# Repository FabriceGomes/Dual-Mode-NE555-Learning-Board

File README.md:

# Dual-Mode-NE555-Learning-Board
A simple NE555 learning board with mono- and bistable modes, made for kids to solder, learn basics, and spark excitement for electronics.

This project presents a custom-designed printed circuit board built around two NE555 timer ICs, arranged to demonstrate two fundamental operating modes of the device. One NE555 is configured in monostable mode, while the second operates in bistable mode. Both circuits are designed to generate a visible one-second blink, making their behavior easy to observe and understand.

A deliberate design choice is the use of the J2 pin header as the trigger interface for the monostable NE555. Instead of implementing a mechanical switch, J2 allows the trigger to be activated using simple jumper caps. This keeps the board cost-effective, reduces mechanical wear, and makes assembly easier for beginners—while still letting participants experiment with trigger control.

The primary purpose of this PCB is educational. It was developed as a hands-on learning platform for children and teenagers, allowing them to solder the components themselves and explore basic electronics in a tangible, engaging way. By assembling the board, young participants learn about resistors, capacitors, integrated circuits, and how these elements interact to create timing functions. The contrasting modes of the two NE555s help illustrate how different circuit configurations lead to different behaviors, even when using the same building block.

Beyond its technical function, the project aims to spark curiosity and confidence in electronics through approachable, practical experience. The board’s layout is intentionally simple, robust, and visually structured to support beginners during assembly, troubleshooting, and experimentation. This combination of clear educational value, functional circuit design, and thoughtful cost-optimized features makes the PCB a versatile tool for workshops, maker events, and introductory electronics courses.

## License
This project is licensed under the MIT License – see the LICENSE file for details.

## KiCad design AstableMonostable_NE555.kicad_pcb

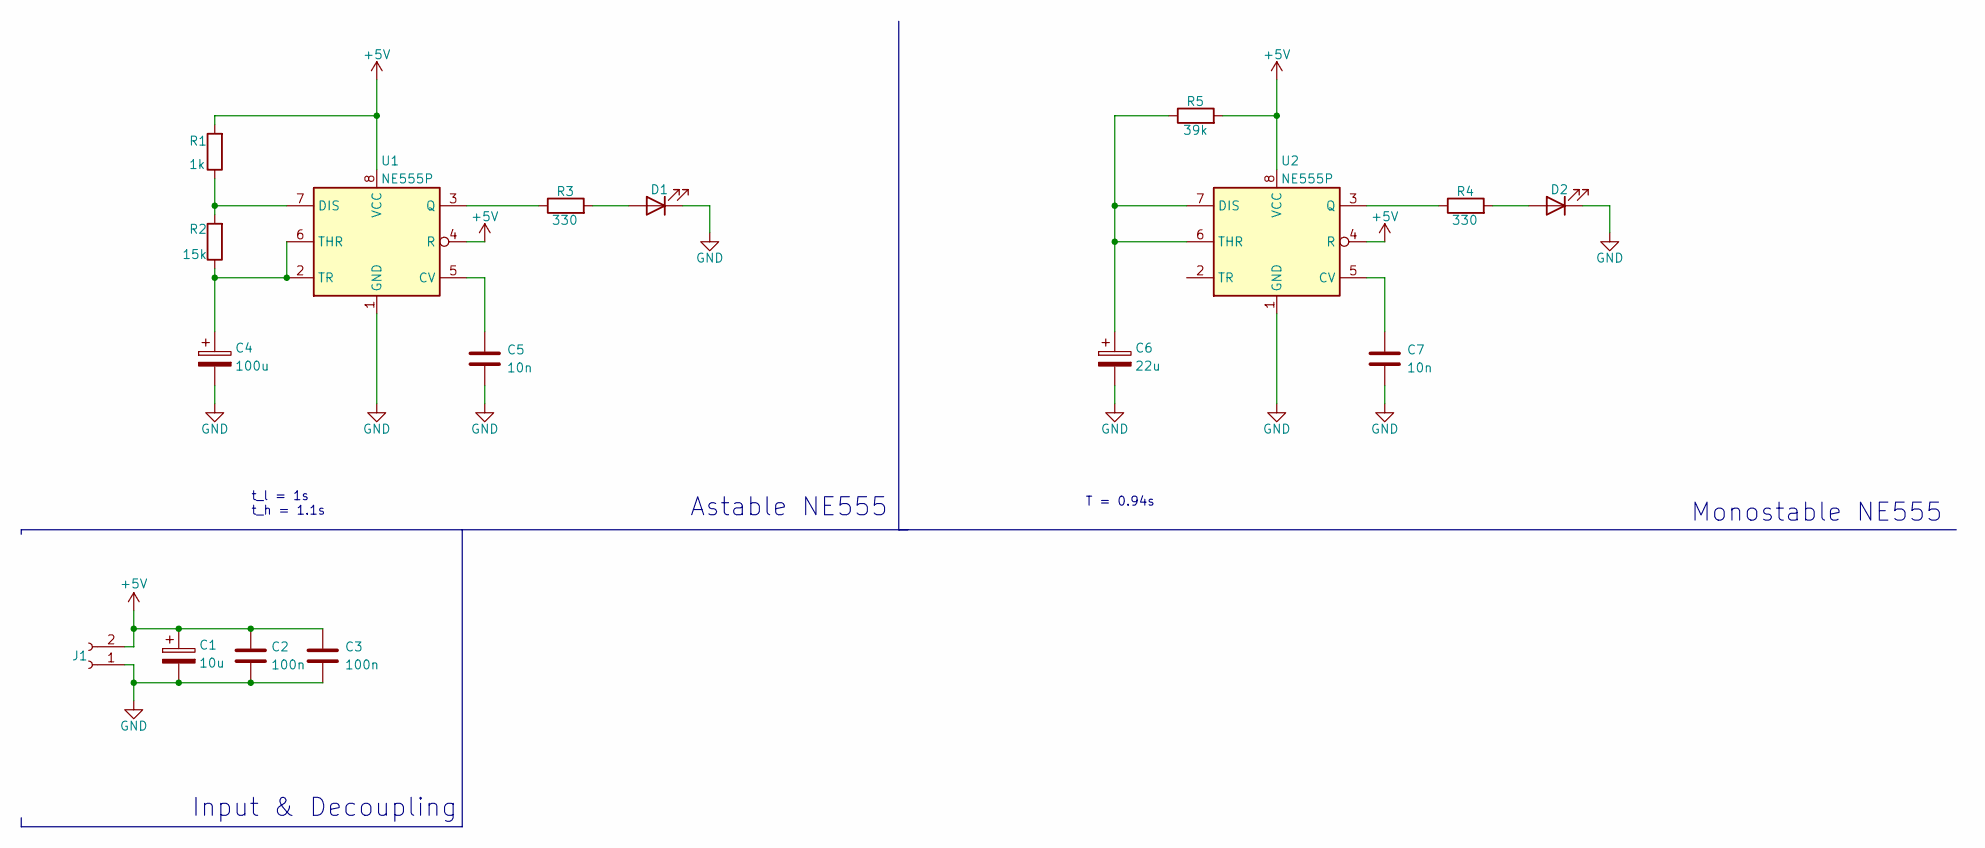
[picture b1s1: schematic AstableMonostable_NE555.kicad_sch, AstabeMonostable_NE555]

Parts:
C1: 10u; CP_Elec_5x5.4
C2, C3: 100n; C_1206_3216Metric_Pad1.33x1.80mm_HandSolder
C4: 100u; CP_Elec_6.3x7.7
C5, C7: 10n; C_1206_3216Metric_Pad1.33x1.80mm_HandSolder
C6: 22u; CP_Elec_4x5.4
D1, D2: Rot; D_1206_3216Metric_Pad1.42x1.75mm_HandSolder
J1: Conn_01x02_Socket; PinSocket_1x02_P2.54mm_Vertical
R1: 1k; R_1206_3216Metric_Pad1.30x1.75mm_HandSolder
R2: 15k; R_1206_3216Metric_Pad1.30x1.75mm_HandSolder
R3, R4: 330; R_1206_3216Metric_Pad1.30x1.75mm_HandSolder
R5: 39k; R_1206_3216Metric_Pad1.30x1.75mm_HandSolder
U1, U2: NE555P; DIP-8_W7.62mm_Socket

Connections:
+5V: C1.1, C2.1, C3.1, J1.2, R1.2, R5.2, U1.4 (R), U1.8 (VCC), U2.4 (R), U2.8 (VCC); also elsewhere on the board
GND: C1.2, C2.2, C3.2, C4.2, C5.2, C6.2, C7.2, D1.1 (K), D2.1 (K), J1.1, U1.1 (GND), U2.1 (GND)
unnamed: D1.2 (A), R3.2
unnamed: D2.2 (A), R4.2
unnamed: C5.1, U1.5 (CV)
unnamed: R1.1, R2.2, U1.7 (DIS)
unnamed: R3.1, U1.3 (Q)
unnamed: C4.1, R2.1, U1.2 (TR), U1.6 (THR)
unnamed: C7.1, U2.5 (CV)
unnamed: C6.1, R5.1, U2.6 (THR), U2.7 (DIS)
unnamed: R4.1, U2.3 (Q)

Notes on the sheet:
Astable NE555
Input & Decoupling
t_l = 1s t_h = 1.1s
Monostable NE555
T = 0.94s

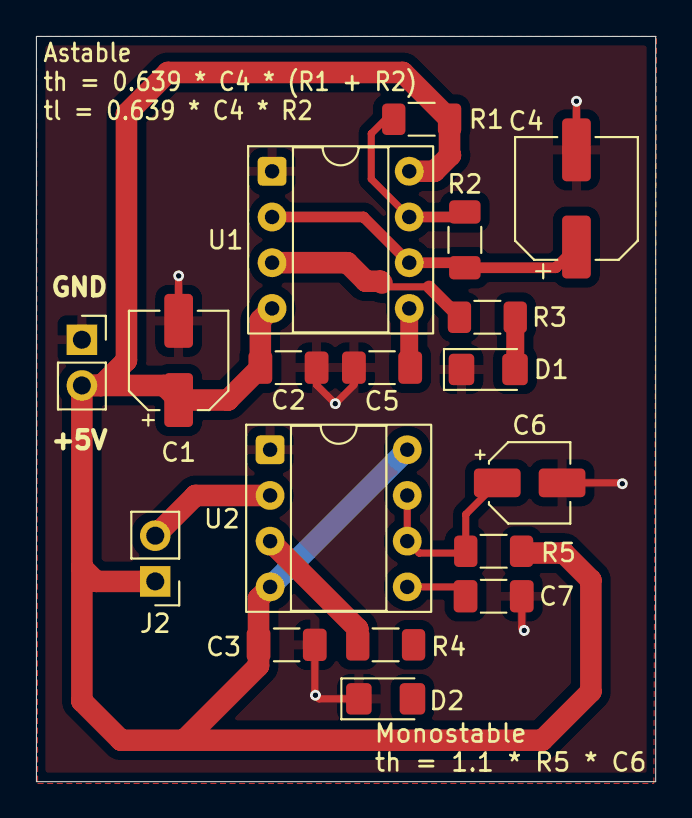
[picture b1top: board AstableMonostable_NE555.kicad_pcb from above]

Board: 2 copper layers, 34.4 x 41.4 mm, 18 parts (0 on the bottom side), 11 nets.

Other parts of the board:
J2: Conn_01x02_Pin; PinHeader_1x02_P2.54mm_Vertical

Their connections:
+5V: J2.1; also elsewhere on the board

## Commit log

2025-11-24 Enhance README with detailed project overview
    Expanded project description to include details about the PCB design, educational purpose, and user-friendly features.
2025-11-24 Clean repo
2025-11-24 Add image to README
2025-11-24 cleaned gitignore
2025-12-22 added LICENSE
2025-12-22 add LICENSE
